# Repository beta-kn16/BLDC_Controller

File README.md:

# BLDC_Controller
Making BLDC controller using stm32g431 and drv8323rs.

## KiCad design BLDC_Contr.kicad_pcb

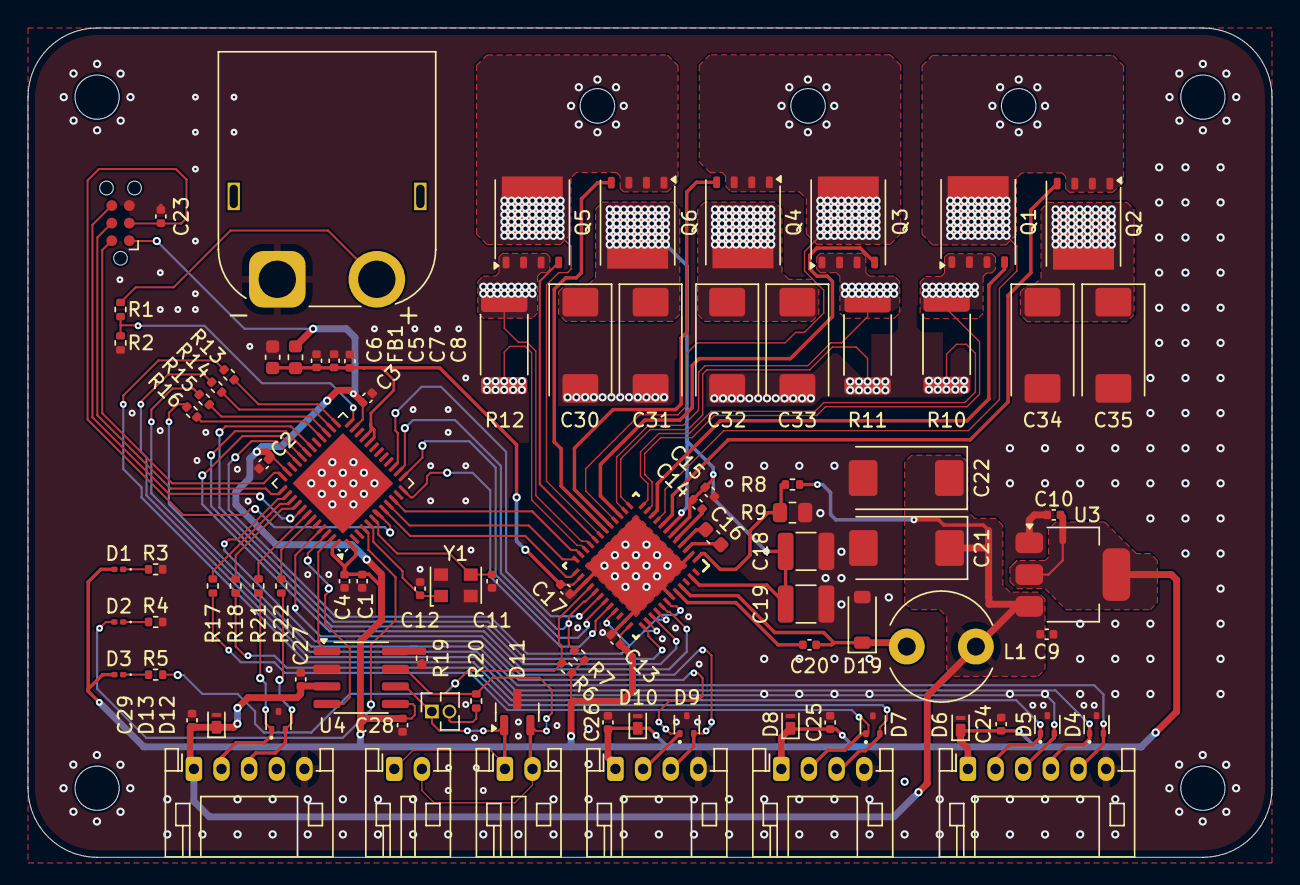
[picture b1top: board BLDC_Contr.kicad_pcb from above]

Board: 4 copper layers, 90.0 x 60.0 mm, 100 parts (0 on the bottom side), 70 nets.

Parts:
C1, C2, C3, C5, C8, C9, C15, C20, C23, C24, C25, C26, C27, C28, C29: 0.1u; C_0402_1005Metric
C4: 4.7u; C_0402_1005Metric
C6: 4.7u; C_0603_1608Metric
C7, C13, C14, C17: 1u; C_0402_1005Metric
C10: 22u; C_0402_1005Metric
C11, C12: 15p; C_0402_1005Metric
C16: 47n; C_0603_1608Metric
C18, C19: 2.2u X7R; C_1210_3225Metric
C21, C22: 15u; CP_EIA-7343-31_Kemet-D
C30, C31, C32, C33, C34, C35: 10u, 50V; CP_EIA-7343-31_Kemet-D
D1, D2: BLUE; LED_0201_0603Metric
D3: RED; LED_0201_0603Metric
D4, D5, D7, D9, D12: ESDA5V3L; SOT-523
D6, D8, D10, D13: D_TVS; Nexperia_DSN1608-2_1.6x0.8mm
D11: D_TVS_Dual_AAC; SOT-23
D19: MBR0580 900mV 2A; D_SOD-123
FB1: FerriteBead_Small; L_0603_1608Metric
H1, H2, H3, H4: MountingHole_Pad_MP; MountingHole_3.2mm_M3
H5, H6, H7: MountingHole_Pad_MP; MountingHole_2.5mm
J1: XT60; AMASS_XT60PW-M_1x02_P7.20mm_Horizontal
J2: Conn_ARM_SWD_TagConnect_TC2030; Tag-Connect_TC2030-IDC-NL_2x03_P1.27mm_Vertical
J3: PH; JST_PH_S6B-PH-K_1x06_P2.00mm_Horizontal
J4, J5: PH; JST_PH_S4B-PH-K_1x04_P2.00mm_Horizontal
J6, J7: PH; JST_PH_S2B-PH-K_1x02_P2.00mm_Horizontal
J8: PIN; PinSocket_1x02_P1.27mm_Vertical
J10: PH; JST_PH_S5B-PH-K_1x05_P2.00mm_Horizontal
L1: 47u; L_Radial_D7.8mm_P5.00mm_Fastron_07HCP
Q1, Q2, Q3, Q4, Q5, Q6: CSD18540Q5B; TDSON-8-1
R1: 110k; R_0402_1005Metric
R2, R6, R7, R19: 10k; R_0402_1005Metric
R3, R4: 15; R_0402_1005Metric
R5, R21, R22: 56; R_0402_1005Metric
R8: 57.6k 1%; R_0402_1005Metric
R9: 10.4k 1%; R_0805_2012Metric
R10, R11, R12: 1m; R_2512_6332Metric
R13, R14, R15, R16, R17, R18, R20: 120; R_0402_1005Metric
U1: STM32G431CBU6; QFN-48-1EP_7x7mm_P0.5mm_EP5.15x5.15mm_ThermalVias
U2: DRV8323RSRGZR; RGZ0048A
U3: AMS1117-3.3; SOT-223-3_TabPin2
U4: SOIC-8_3.9x4.9mm_P1.27mm
Y1: Crystal_16Mhz; Oscillator_SMD_EuroQuartz_XO32-4Pin_3.2x2.5mm

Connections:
+3.3V: C1.1, C2.1, C3.1, C4.1, C10.1, C13.1, C24.1, C25.1, C26.1, C28.1, D1.2 (A), D3.2 (A), D6.1 (K), D8.1 (K), D10.1 (K), FB1.1, J2.1 (VCC), J3.1, J4.1, J5.1, R6.1, R7.1, U1.1 (VBAT), U1.23 (VDD), U1.35 (VDD), U1.48 (VDD), U2.36 (DVDD), U3.2 (VO), U4.5 (VIO)
+3.3VA: C5.1, C6.1, C7.1, C8.1, C17.1, FB1.2, U1.20 (VREF+), U1.21 (VDDA), U2.26 (VREF)
+5V: C9.1, C21.1, C22.1, C27.1, C29.1, D13.1 (K), J10.1, L1.2, R8.1, U3.3 (VI), U4.3 (VCC)
+BATT: C14.2, C15.2, C18.1, C19.1, C30.1, C31.1, C32.1, C33.1, C34.1, C35.1, J1.2, Q2.5 (D), Q4.5 (D), Q6.5 (D), R1.1, U2.6 (VM), U2.7 (VDRAIN), U2.47 (VIN)
/AMT_A_C: D12.1 (K), J10.2, R21.2
/AMT_B_C: D12.2 (K), J10.3, R22.2
/CAN_H_C: D11.2 (A2), J6.2, J7.2, R20.1, U4.7 (CANH)
/CAN_L_C: D11.1 (A1), J6.1, J7.1, J8.1, U4.6 (CANL)
/CAN_R_J: J8.2, R20.2
/CB: C20.1, U2.44 (CB)
/CPH: C16.1, U2.4 (CPH)
/CPL: C16.2, U2.3 (CPL)
/FB: R8.2, R9.1, U2.1 (FB)
/LED_B_R1: D1.1 (K), R3.1
/LED_B_R2: D2.1 (K), R4.1
/LED_R_R: D3.1 (K), R5.1
/SPI2_MISO_C: D4.1 (K), J3.4, R15.2
/SPI2_MOSI_C: D4.2 (K), J3.5, R16.1
/SPI2_NCS_C: D5.1 (K), J3.2, R13.1
/SPI2_SCK_C: D5.2 (K), J3.3, R14.2
/SW: C20.2, D19.1 (K), L1.1, U2.45 (SW)
/UART_RX_C: D7.1 (K), J4.2, R17.2
/UART_TX_C: D7.2 (K), J4.3, R18.2
/VCP: C14.1, U2.5 (VCP)
AMT_A: R21.1, U1.42 (PB4)
AMT_B: R22.1, U1.43 (PB5)
CAN_RX: U1.46 (PB8), U4.4 (RXD)
CAN_TX: U1.47 (PB9), U4.1 (TXD)
GHA: Q2.4 (G), U2.8 (GHA)
GHB: Q4.4 (G), U2.17 (GHB)
GHC: Q6.4 (G), U2.18 (GHC)
GLA: Q1.4 (G), U2.10 (GLA)
GLB: Q3.4 (G), U2.15 (GLB)
GLC: Q5.4 (G), U2.20 (GLC)
GND: C1.2, C2.2, C3.2, C4.2, C5.2, C6.2, C7.2, C8.2, C9.2, C10.2, C11.2, C12.2, C13.2, C15.1, C17.2, C18.2, C19.2, C21.2, C22.2, C23.2, C24.2, C25.2, C26.2, C27.2, C28.2, C29.2, C30.2, C31.2, C32.2, C33.2, C34.2, C35.2, D4.3 (A), D5.3 (A), D6.2 (A), D7.3 (A), D8.2 (A), D9.3 (A), D10.2 (A), D11.3 (common), D12.3 (A), D13.2 (A), D19.2 (A), J1.1, J2.5 (GND), J3.6, J4.4, J5.4, J10.5, R2.2, R3.2, R4.2, R9.2, R10.2, R11.2, R12.2, R19.2, U1.49 (VSS), U2.2 (PGND), U2.12 (SNA), U2.13 (SNB), U2.22 (SNC), U2.27 (DGND), U2.35 (AGND), U2.43 (BGND), U2.49 (PAD), U3.1 (GND), U4.2 (GND), Y1.2, Y1.4
HSE_IN: C12.1, U1.5 (PF0), Y1.1
HSE_OUT: C11.1, U1.6 (PF1), Y1.3
I2C_SCL: D9.1 (K), J5.2, U1.38 (PA15)
I2C_SDA: D9.2 (K), J5.3, U1.45 (PB7)
INHA: U1.30 (PA8), U2.37 (INHA)
INHB: U1.31 (PA9), U2.39 (INHB)
INHC: U1.32 (PA10), U2.41 (INHC)
MOTOR_HiZ: U1.33 (PA11), U2.33 (ENABLE), U2.38 (INLA), U2.40 (INLB), U2.42 (INLC)
NFAULT_PRE: R5.2, R6.2, U2.28 (nFAULT)
NRST: C23.1, J2.3 (~RESET), U1.7 (PG10)
unnamed: R19.1, U4.8 (S)
RX: R18.1, U1.40 (PC11)
SHA: Q1.5 (D), Q2.1 (S), Q2.2 (S), Q2.3 (S), U2.9 (SHA)
SHB: Q3.5 (D), Q4.1 (S), Q4.2 (S), Q4.3 (S), U2.16 (SHB)
SHC: Q5.5 (D), Q6.1 (S), Q6.2 (S), Q6.3 (S), U2.19 (SHC)
SOA: U1.8 (PA0), U2.25 (SOA)
SOB: U1.9 (PA1), U2.24 (SOB)
SOC: U1.10 (PA2), U2.23 (SOC)
SP1_MISO: R7.2, U1.14 (PA6), U2.29 (SDO)
SP1_MOSI: U1.15 (PA7), U2.30 (SDI)
SP1_NCS: U1.12 (PA4), U2.32 (nSCS)
SP1_SCK: U1.13 (PA5), U2.31 (SCLK)
SP2_MISO: R15.1, U1.27 (PB14)
SP2_MOSI: R16.2, U1.28 (PB15)
SP2_NCS: R13.2, U1.25 (PB12)
SP2_SCK: R14.1, U1.26 (PB13)
SPA: Q1.1 (S), Q1.2 (S), Q1.3 (S), R10.1, U2.11 (SPA)
SPB: Q3.1 (S), Q3.2 (S), Q3.3 (S), R11.1, U2.14 (SPB)
SPC: Q5.1 (S), Q5.2 (S), Q5.3 (S), R12.1, U2.21 (SPC)
SWCLK: J2.4 (SWCLK), U1.37 (PA14)
SWDIO: J2.2 (SWDIO), U1.36 (PA13)
SWO: J2.6 (SWO), U1.41 (PB3)
TX: R17.1, U1.39 (PC10)
USER_LED: D2.2 (A), U1.4 (PC15)
VIN_DIVIDER: R1.2, R2.1, U1.24 (PB11)

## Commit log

2025-08-22 initialized and added files
2025-08-24 add PCB layouts
2025-08-25 add wiring. changed communication of spi on drv8323 from spi2 to spi1 for better wiring.
2025-08-26 added most wiring, not erc checked. changed pinouts on connectors for easier wiring
2025-08-26 wired every component, ground poured doing erc (not done yet)
2025-08-27 changed most 0603 parts to 0402. wiring changed. pcb dimesion from 65*80mm to 60*80mm
2025-08-27 DRCing not done
2025-08-28 changed most 0603 parts to 0402. wiring changed. pcb dimesion from 65*80mm to 60*80m
2025-08-28 pcb gerber made. checking for errors. add gnd vias
